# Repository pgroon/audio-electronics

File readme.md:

# Audio Electronics

This is a collection of electronics for audio projects, in various stages of completion.

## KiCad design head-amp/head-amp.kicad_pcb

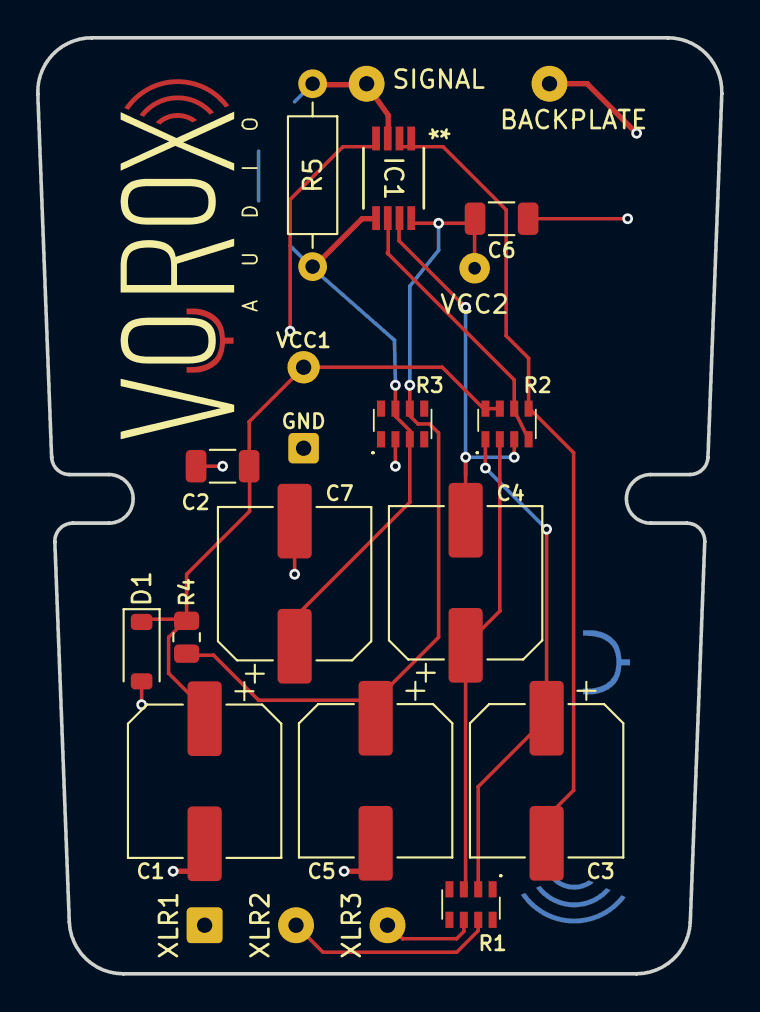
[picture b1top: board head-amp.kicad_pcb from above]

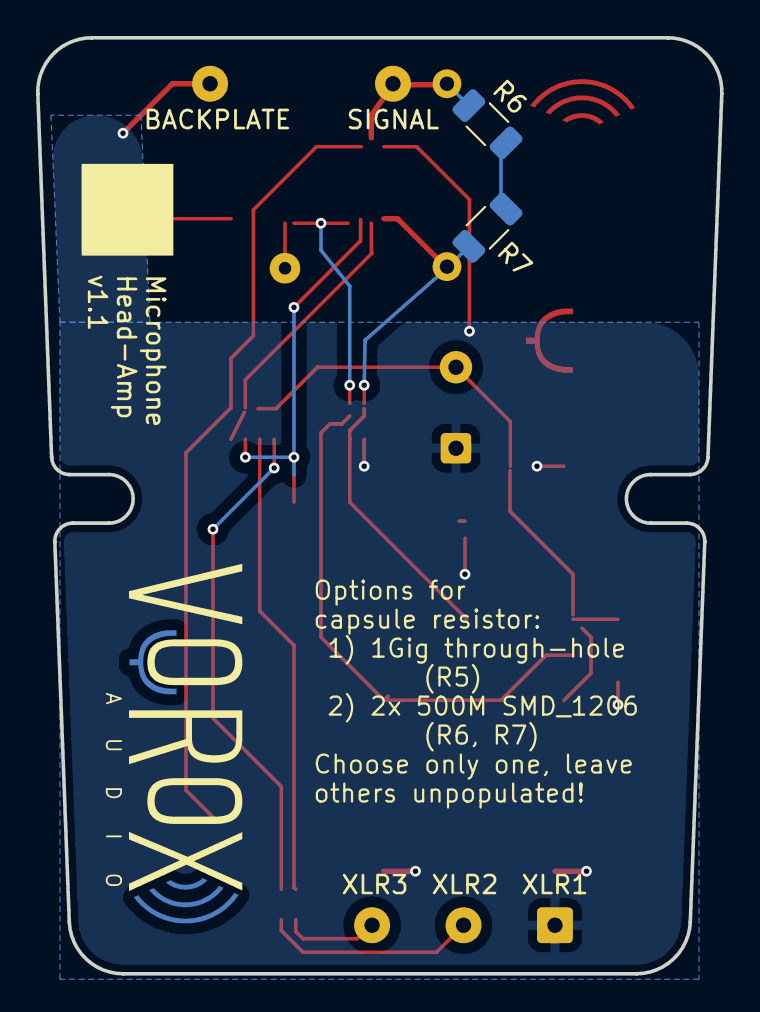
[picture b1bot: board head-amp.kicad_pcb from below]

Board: 2 copper layers, 38.0 x 52.0 mm, 24 parts (2 on the bottom side), 13 nets.

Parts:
BACKPLATE: Conn_01x01_Pin; SolderWire-0.25sqmm_1x01_D0.65mm_OD2mm
C1, C3, C4, C5, C7: 47uF; CP_Elec_8x6.9
C2, C6: 100nF; C_1206_3216Metric
D1: Zener_12V; D_SOD-123
GND: TestPoint; SolderWire-0.15sqmm_1x01_D0.5mm_OD1.5mm
IC1: OPA1642AID; DGK8
R1: 47; YC164JR072K2L
R2: 2k2; YC164JR072K2L
R3: 47k; YC164JR072K2L
R4: 220; R_0805_2012Metric
R5: 1G; R_Axial_DIN0207_L6.3mm_D2.5mm_P10.16mm_Horizontal
R6, R7: 500M; R_1206_3216Metric
SIGNAL: Conn_01x01_Pin; SolderWire-0.25sqmm_1x01_D0.65mm_OD2mm
VCC1, VCC2: TestPoint; SolderWire-0.15sqmm_1x01_D0.5mm_OD1.5mm
XLR1, XLR2, XLR3: Conn_01x01_Pin; SolderWire-0.25sqmm_1x01_D0.65mm_OD2mm

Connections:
GND: BACKPLATE.1, C1.2, C2.2, C5.2, C6.2, C7.2, D1.2 (A), GND.1, IC1.4 (V-), R3.2, XLR1.1
unnamed: C3.1, R1.2, R2.1
unnamed: C4.1, R1.3, R2.2
unnamed: C1.1, C2.1, D1.1 (K), R2.7, R2.8, R4.1, VCC1.1
unnamed: IC1.3 (+IN_A), R5.1, R6.1, SIGNAL.1
unnamed: C7.1, IC1.5 (+IN_B), R3.3, R3.7, R5.2, R7.2
unnamed: C3.2, IC1.1 (OUT_A), IC1.2 (-IN_A), R2.5
unnamed: IC1.6 (-IN_B), R2.4, R2.6
unnamed: C4.2, IC1.7 (OUT_B), R2.3
unnamed: C5.1, C6.1, IC1.8 (V+), R3.6, R4.2, VCC2.1
unnamed: R6.2, R7.1
unnamed: R1.7, XLR2.1
unnamed: R1.6, XLR3.1

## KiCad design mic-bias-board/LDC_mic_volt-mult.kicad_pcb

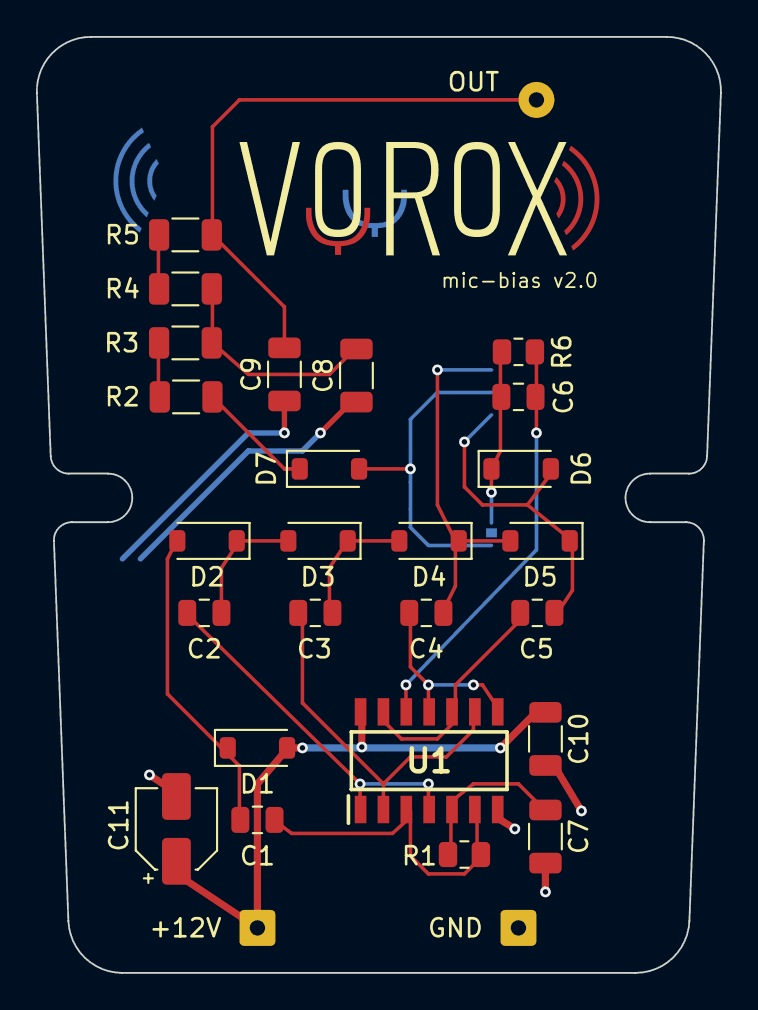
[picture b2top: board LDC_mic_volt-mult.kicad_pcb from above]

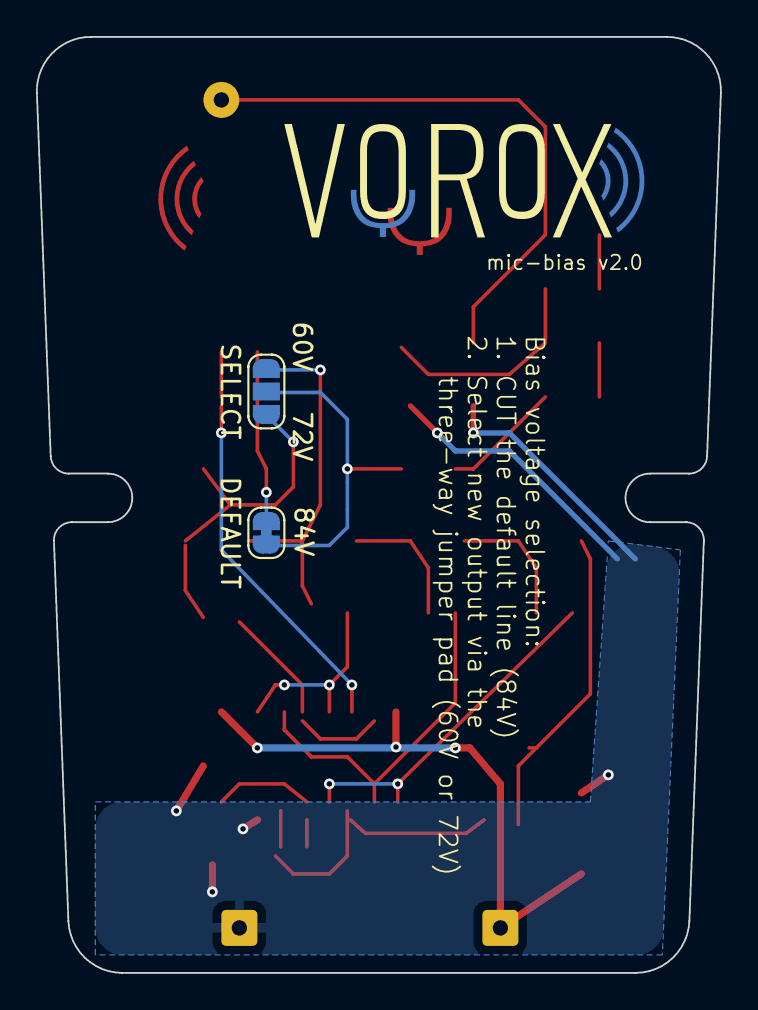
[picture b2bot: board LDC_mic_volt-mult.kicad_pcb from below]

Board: 2 copper layers, 38.0 x 52.0 mm, 30 parts (2 on the bottom side), 21 nets, no tracks yet.

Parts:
+12V: SolderWire-0.25sqmm_1x01_D0.65mm_OD2mm
C1, C2, C3, C4, C5, C6: 10nF; C_0805_2012Metric
C7: 1nF; C_1206_3216Metric
C8, C9, C10: 100nF; C_1206_3216Metric
C11: 4,7uF; CP_Elec_4x5.4
D1, D2, D3, D4, D5, D6, D7: 1N4148W; D_SOD-123
DEFAULT: SolderJumper_2_Bridged; SolderJumper-2_P1.3mm_Bridged_RoundedPad1.0x1.5mm
GND: SolderWire-0.25sqmm_1x01_D0.65mm_OD2mm
OUT: SolderWire-0.25sqmm_1x01_D0.65mm_OD2mm
R1: 10k; R_0805_2012Metric
R2, R3, R4, R5: 510k; R_1206_3216Metric
R6: 100M; R_0805_2012Metric
SELECT: SolderJumper_3_Open; SolderJumper-3_P1.3mm_Open_RoundedPad1.0x1.5mm_NumberLabels
U1: HCF40106_Hex-Inverter; SOIC127P600X175-14N

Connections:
GND: C7.2, C8.1, C9.1, C10.2, C11.2, GND.1, U1.7 (GND)
unnamed: C8.2, R3.1, R4.2
unnamed: C9.2, OUT.1, R5.1
unnamed: +12V.1, C10.1, C11.1, D1.2 (A), U1.14 (VCC)
unnamed: C1.1, D1.1 (K), D2.2 (A)
unnamed: C2.1, D2.1 (K), D3.2 (A)
unnamed: C3.1, D3.1 (K), D4.2 (A)
unnamed: C4.1, D4.1 (K), D5.2 (A), SELECT.3 (B)
unnamed: C5.1, D5.1 (K), D6.2 (A), SELECT.1 (A)
unnamed: C6.1, D6.1 (K), DEFAULT.1 (A), R6.1
unnamed: D7.2 (A), DEFAULT.2 (B), SELECT.2 (C)
unnamed: D7.1 (K), R2.2
unnamed: R2.1, R3.2
unnamed: R4.1, R5.2
unnamed: C2.2, U1.1 (A), U1.4 (H)
unnamed: C3.2, U1.2 (G), U1.9 (D)
unnamed: C1.2, R1.1, U1.3 (B), U1.6 (I)
unnamed: C7.1, R1.2, U1.5 (C)
unnamed: C4.2, U1.8 (J), U1.11 (E)
unnamed: C5.2, U1.10 (K), U1.13 (F)
unnamed: C6.2, R6.2, U1.12 (L)

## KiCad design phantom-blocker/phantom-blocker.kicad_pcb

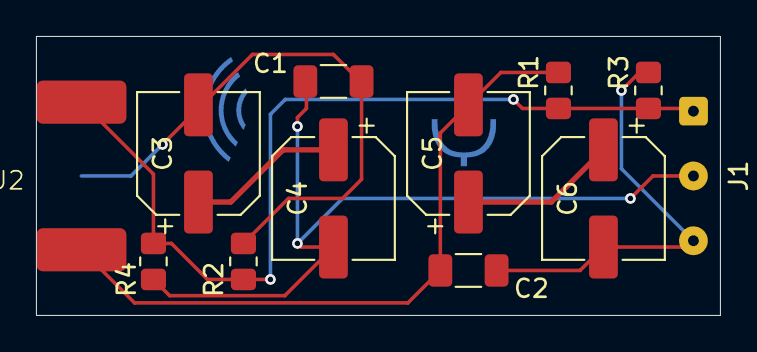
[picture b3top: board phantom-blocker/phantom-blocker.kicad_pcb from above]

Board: 2 copper layers, 38.0 x 15.5 mm, 12 parts (0 on the bottom side), 7 nets.

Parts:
C1, C2: 100nF 63V; C_1206_3216Metric_Pad1.33x1.80mm_HandSolder
C3, C4, C5, C6: 22uF 63V; CP_Elec_6.3x7.7
J1: XLR3 - Microphone; SolderWire-0.1sqmm_1x03_P3.6mm_D0.4mm_OD1mm
J2: XLR3 - Mixer; XLR-Pin-SolderPad
R1, R2: 47k; R_0805_2012Metric_Pad1.20x1.40mm_HandSolder
R3, R4: 1M; R_0805_2012Metric_Pad1.20x1.40mm_HandSolder

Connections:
unnamed: C1.1, C3.2, J2.3, R2.2
unnamed: C1.2, C4.2, J1.3, R4.2
unnamed: C2.1, C5.2, J2.2, R1.2
unnamed: C2.2, C6.2, J1.2, R3.2
unnamed: C3.1, C4.1
unnamed: C5.1, C6.1
unnamed: J1.1, J2.1, R1.1, R2.1, R3.1, R4.1

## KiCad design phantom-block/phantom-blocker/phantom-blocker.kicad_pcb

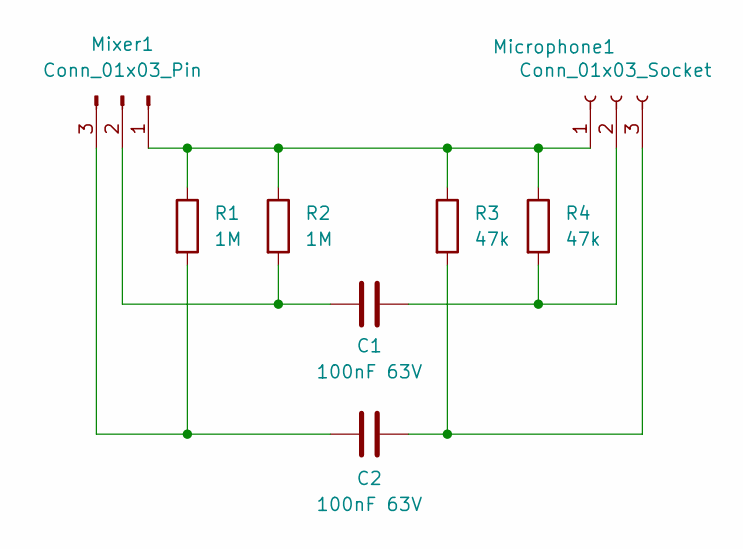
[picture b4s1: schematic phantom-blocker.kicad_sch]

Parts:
C1, C2: 100nF 63V; C_1206_3216Metric_Pad1.33x1.80mm_HandSolder
Microphone1: Conn_01x03_Socket; SolderWire-0.1sqmm_1x03_P3.6mm_D0.4mm_OD1mm
Mixer1: Conn_01x03_Pin; XLR-Pin-SolderPad
R1, R2: 1M; R_0805_2012Metric_Pad1.20x1.40mm_HandSolder
R3, R4: 47k; R_0805_2012Metric_Pad1.20x1.40mm_HandSolder

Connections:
unnamed: Microphone1.1, Mixer1.1, R1.1, R2.1, R3.1, R4.1
unnamed: C1.2, Microphone1.2, R4.2
unnamed: C2.2, Microphone1.3, R3.2
unnamed: C1.1, Mixer1.2, R2.2
unnamed: C2.1, Mixer1.3, R1.2

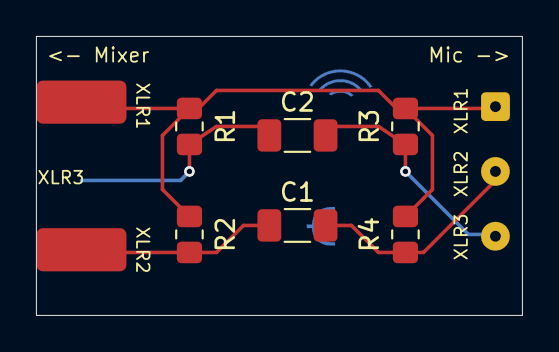
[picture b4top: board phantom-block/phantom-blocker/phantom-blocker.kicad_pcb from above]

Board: 2 copper layers, 27.0 x 15.5 mm, 8 parts (0 on the bottom side), 5 nets.

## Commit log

2026-01-24 Completed version 2 of the bias voltage board with jumper-selectable voltage.
2026-01-25 Added panel version of PCB
2026-01-30 v1.0 of phantom blocker board done
2026-02-11 Microphone head-amp initial commit
2026-02-11 Finished head amp PCB layout, generated gerber + BOM
2026-02-13 added gitignore and kikit panelization config sample file
2026-02-13 Added kikit panel files for two completed projects
2026-03-14 backing up current state
2026-04-09 input/output connectors moved to 2.54mm spacing. Improved clearance around screw slots.
2026-04-09 updated logo footprint
